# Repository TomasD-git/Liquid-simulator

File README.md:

# Liquid-simulator
Basically simulates liquid using imu and esp32 C6

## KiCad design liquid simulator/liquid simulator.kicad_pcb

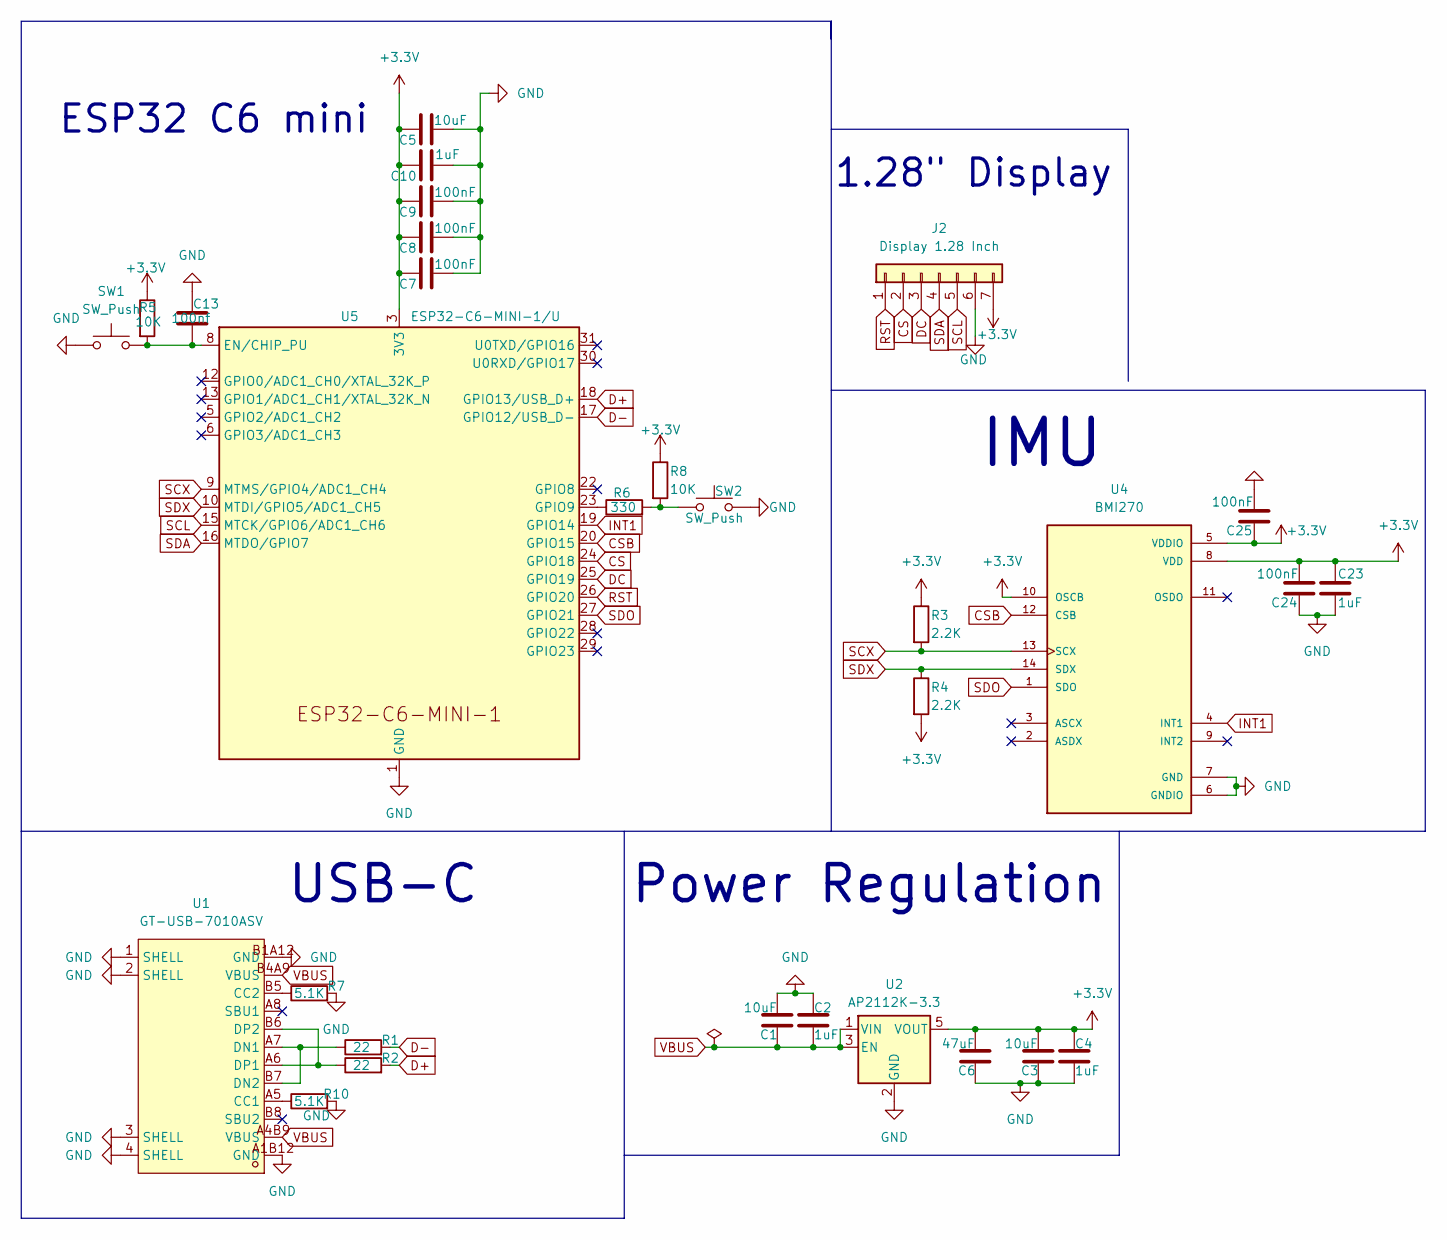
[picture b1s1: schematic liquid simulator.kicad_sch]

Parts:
C1, C3, C5: 10uF; C_0603_1608Metric
C2, C4: 1uF; C_0603_1608Metric
C6: 47uF; C_0805_2012Metric
C7, C8, C9, C24, C25: 100nF; C_0402_1005Metric
C10, C23: 1uF; C_0402_1005Metric
C13: 100nf; C_0402_1005Metric
J2: Display 1.28 Inch; PinHeader_1x07_P2.54mm_Vertical
R1, R2: 22; R_0402_1005Metric
R3, R4: 2.2K; R_0402_1005Metric
R5, R8: 10K; R_0402_1005Metric
R6: 330; R_0402_1005Metric
R7, R10: 5.1K; R_0402_1005Metric
SW1, SW2: SW_Push; SW_Push_1P1T_XKB_TS-1187A
U1: GT-USB-7010ASV; USB-C-SMD_G-SWITCH_GT-USB-7010ASV; MPN GT-USB-7010ASV; LCSC Part C2988369
U2: AP2112K-3.3; SOT-23-5
U4: BMI270; XDCR_BMI270
U5: ESP32-C6-MINI-1/U; ESP32-C6-MINI-1

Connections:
+3.3V: C3.1, C4.1, C5.1, C6.1, C7.1, C8.1, C9.1, C10.1, C23.1, C24.1, C25.2, J2.7, R3.1, R4.2, R5.1, R8.1, U2.5 (VOUT), U4.5 (VDDIO), U4.8 (VDD), U4.10 (OSCB), U5.3 (3V3)
CS: J2.2, U5.24 (GPIO18)
CSB: U4.12 (CSB), U5.20 (GPIO15)
D+: R2.2, U5.18 (GPIO13/USB_D+)
D-: R1.2, U5.17 (GPIO12/USB_D-)
DC: J2.3, U5.25 (GPIO19)
GND: C1.1, C2.1, C3.2, C4.2, C5.2, C6.2, C7.2, C8.2, C9.2, C10.2, C13.1, C23.2, C24.2, C25.1, J2.6, R7.2, R10.2, SW1.1, SW2.2, U1.1 (SHELL), U1.2 (SHELL), U1.3 (SHELL), U1.4 (SHELL), U1.A1B12 (GND), U1.B1A12 (GND), U2.2 (GND), U4.6 (GNDIO), U4.7 (GND), U5.1 (GND), U5.2 (GND), U5.11 (GND), U5.14 (GND), U5.36 (GND), U5.37 (GND), U5.38 (GND), U5.39 (GND), U5.40 (GND), U5.41 (GND), U5.42 (GND), U5.43 (GND), U5.44 (GND), U5.45 (GND), U5.46 (GND), U5.47 (GND), U5.48 (GND), U5.49 (GND), U5.50 (GND), U5.51 (GND), U5.52 (GND), U5.53 (GND)
INT1: U4.4 (INT1), U5.19 (GPIO14)
unnamed: R6.2, R8.2, SW2.1
unnamed: R10.1, U1.A5 (CC1)
unnamed: R7.1, U1.B5 (CC2)
unnamed: R1.1, U1.A7 (DN1), U1.B7 (DN2)
unnamed: R2.1, U1.A6 (DP1), U1.B6 (DP2)
unnamed: C13.2, R5.2, SW1.2, U5.8 (EN/CHIP_PU)
unnamed: R6.1, U5.23 (GPIO9)
RST: J2.1, U5.26 (GPIO20)
SCL: J2.5, U5.15 (MTCK/GPIO6/ADC1_CH6)
SCX: R3.2, U4.13 (SCX), U5.9 (MTMS/GPIO4/ADC1_CH4)
SDA: J2.4, U5.16 (MTDO/GPIO7)
SDO: U4.1 (SDO), U5.27 (GPIO21)
SDX: R4.1, U4.14 (SDX), U5.10 (MTDI/GPIO5/ADC1_CH5)
VBUS: C1.2, C2.2, U1.A4B9 (VBUS), U1.B4A9 (VBUS), U2.1 (VIN), U2.3 (EN)

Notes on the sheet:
IMU
ESP32 C6 mini
Power Regulation
1.28" Display
USB-C

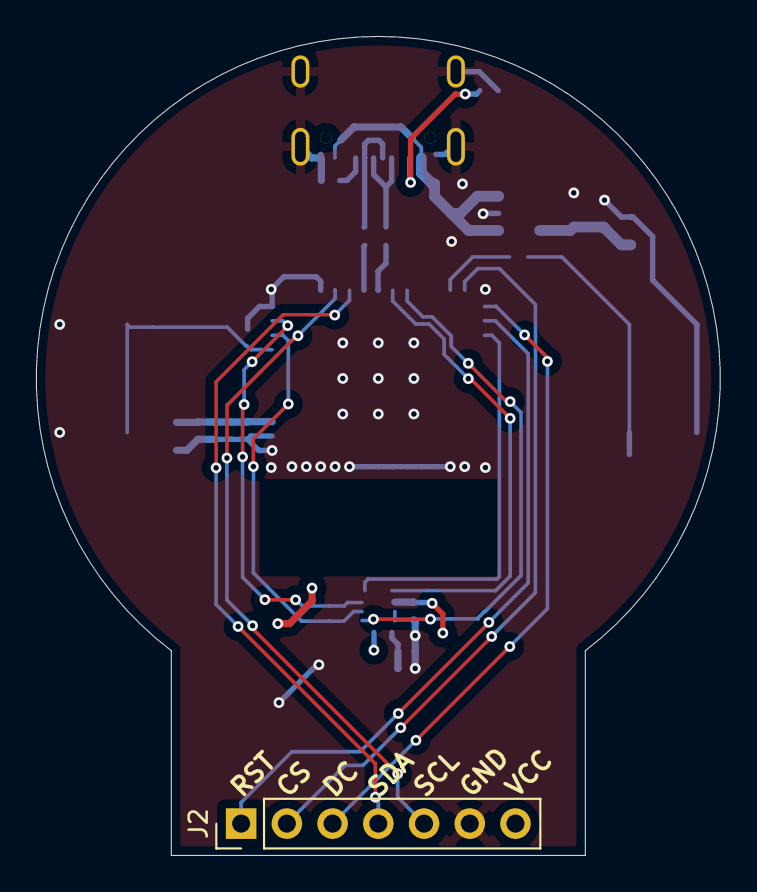
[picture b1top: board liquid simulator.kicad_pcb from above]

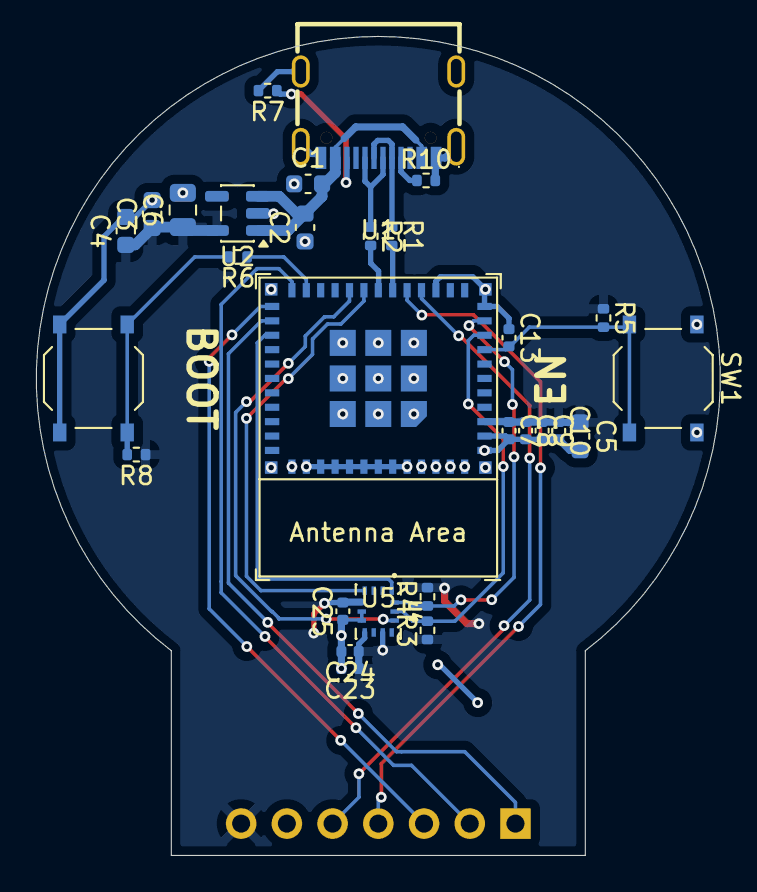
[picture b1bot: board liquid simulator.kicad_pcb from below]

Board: 2 copper layers, 38.0 x 45.5 mm, 30 parts (29 on the bottom side), 22 nets.

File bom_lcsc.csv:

Designator,Footprint,Quantity,Value,LCSC Part #
"C1, C3, C5",0603,3,10uF,C1691
"C10, C23",0402,2,1uF,C52923
"C13, C24, C25, C7, C8, C9",0402,6,100nf,C1525
"C2, C4",0603,2,1uF,C15849
C6,0805,1,47uF,C16780
J2,PinHeader_1x07_P2.54mm_Vertical,1,Display 1.28 Inch,
"R1, R2",0402,2,22,C25092
"R10, R7",0402,2,5.1K,C25905
"R3, R4",0402,2,2.2K,C25879
"R5, R8",0402,2,10K,C25744
R6,0402,1,330,C25104
"SW1, SW2",SW_Push_1P1T_XKB_TS-1187A,2,SW_Push,C318884
U1,USB-C-SMD_G-SWITCH_GT-USB-7010ASV,1,GT-USB-7010ASV,C2988369
U2,SOT-23-5,1,AP2112K-3.3,C51118
U4,XDCR_BMI270,1,BMI270,C2836813
U5,ESP32-C6-MINI-1,1,ESP32-C6-MINI-1/U,C5736265

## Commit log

2026-05-26 Added firmware
2026-05-26 added schematic + bom_lcsc
2026-05-26 added pcb file
2026-05-26 added main BOM
2026-05-26 Add images to README for better visualization
    Added images to enhance the README with visual content.
